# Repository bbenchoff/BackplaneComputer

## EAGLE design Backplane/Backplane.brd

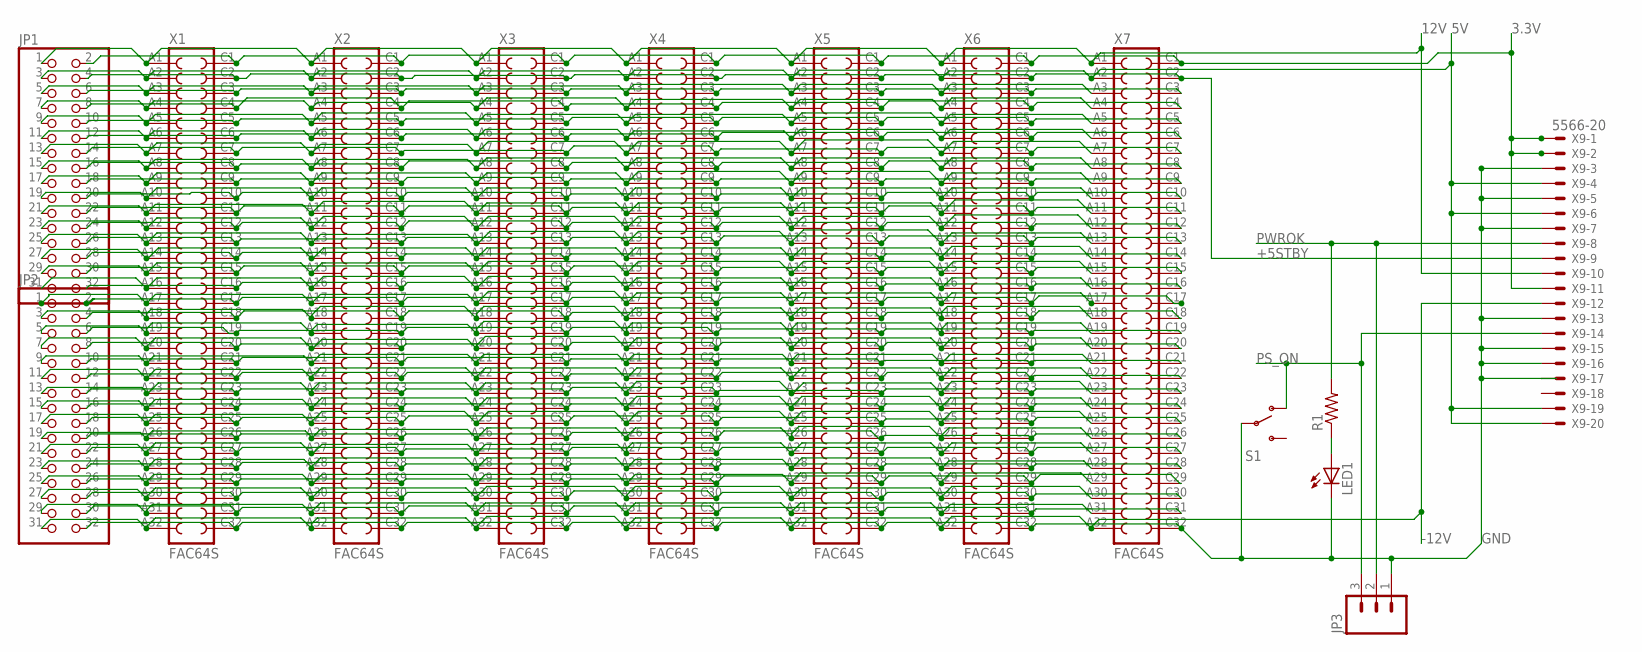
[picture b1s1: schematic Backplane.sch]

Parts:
JP1, JP2: PINHD-2X16; 2X16
JP3: M03LONGPADS; 1X03_LONGPADS
LED1: LED3MM
R1: RESISTORKIT; AXIAL-0.3-KIT
S1: SWITCH-SPDTPTH; SWITCH-SPDT
X1, X2, X3, X4, X5, X6, X7: FAC64S
X9: 5566-20

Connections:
3.3V: JP1.2, X1.C1, X2.C1, X3.C1, X4.C1, X5.C1, X6.C1, X7.C1, X9.1, X9.2, X9.11
5V: JP1.3, X1.A2, X2.A2, X3.A2, X4.A2, X5.A2, X6.A2, X7.A2, X9.4, X9.6, X9.19, X9.20
12V: JP1.1, X1.A1, X2.A1, X3.A1, X4.A1, X5.A1, X6.A1, X7.A1, X9.10
+5STBY: JP1.4, X1.C2, X2.C2, X3.C2, X4.C2, X5.C2, X6.C2, X7.C2, X9.9
-12V: JP2.31, X1.A32, X2.A32, X3.A32, X4.A32, X5.A32, X6.A32, X7.A32, X9.12
GND: JP2.32, JP3.1, LED1.K (C), S1.2, X1.C32, X2.C32, X3.C32, X4.C32, X5.C32, X6.C32, X7.C32, X9.3, X9.5, X9.7, X9.13, X9.15, X9.16
unnamed: LED1.A, R1.P$1 (1)
unnamed: JP1.5, X1.A3, X2.A3, X3.A3, X4.A3, X5.A3, X6.A3, X7.A3
unnamed: JP1.6, X1.C3, X2.C3, X3.C3, X4.C3, X5.C3, X6.C3, X7.C3
unnamed: JP1.7, X1.A4, X2.A4, X3.A4, X4.A4, X5.A4, X6.A4, X7.A4
unnamed: JP1.8, X1.C4, X2.C4, X3.C4, X4.C4, X5.C4, X6.C4, X7.C4
unnamed: JP1.9, X1.A5, X2.A5, X3.A5, X4.A5, X5.A5, X6.A5, X7.A5
unnamed: JP1.10, X1.C5, X2.C5, X3.C5, X4.C5, X5.C5, X6.C5, X7.C5
unnamed: JP1.11, X1.A6, X2.A6, X3.A6, X4.A6, X5.A6, X6.A6, X7.A6
unnamed: JP1.12, X1.C6, X2.C6, X3.C6, X4.C6, X5.C6, X6.C6, X7.C6
unnamed: JP1.13, X1.A7, X2.A7, X3.A7, X4.A7, X5.A7, X6.A7, X7.A7
unnamed: JP1.14, X1.C7, X2.C7, X3.C7, X4.C7, X5.C7, X6.C7, X7.C7
unnamed: JP1.15, X1.A8, X2.A8, X3.A8, X4.A8, X5.A8, X6.A8, X7.A8
unnamed: JP1.16, X1.C8, X2.C8, X3.C8, X4.C8, X5.C8, X6.C8, X7.C8
unnamed: JP1.17, X1.A9, X2.A9, X3.A9, X4.A9, X5.A9, X6.A9, X7.A9
unnamed: JP1.18, X1.C9, X2.C9, X3.C9, X4.C9, X5.C9, X6.C9, X7.C9
unnamed: JP1.19, X1.A10, X2.A10, X3.A10, X4.A10, X5.A10, X6.A10, X7.A10
unnamed: JP1.20, X1.C10, X2.C10, X3.C10, X4.C10, X5.C10, X6.C10, X7.C10
unnamed: JP1.21, X1.A11, X2.A11, X3.A11, X4.A11, X5.A11, X6.A11, X7.A11
unnamed: JP1.22, X1.C11, X2.C11, X3.C11, X4.C11, X5.C11, X6.C11, X7.C11
unnamed: JP1.23, X1.A12, X2.A12, X3.A12, X4.A12, X5.A12, X6.A12, X7.A12
unnamed: JP1.24, X1.C12, X2.C12, X3.C12, X4.C12, X5.C12, X6.C12, X7.C12
unnamed: JP1.25, X1.A13, X2.A13, X3.A13, X4.A13, X5.A13, X6.A13, X7.A13
unnamed: JP1.26, X1.C13, X2.C13, X3.C13, X4.C13, X5.C13, X6.C13, X7.C13
unnamed: JP1.27, X1.A14, X2.A14, X3.A14, X4.A14, X5.A14, X6.A14, X7.A14
unnamed: JP1.28, X1.C14, X2.C14, X3.C14, X4.C14, X5.C14, X6.C14, X7.C14
unnamed: JP1.29, X1.A15, X2.A15, X3.A15, X4.A15, X5.A15, X6.A15, X7.A15
unnamed: JP1.30, X1.C15, X2.C15, X3.C15, X4.C15, X5.C15, X6.C15, X7.C15
unnamed: JP1.31, X1.A16, X2.A16, X3.A16, X4.A16, X5.A16, X6.A16, X7.A16
unnamed: JP1.32, X1.C16, X2.C16, X3.C16, X4.C16, X5.C16, X6.C16, X7.C16
unnamed: JP2.1, X1.A17, X2.A17, X3.A17, X4.A17, X5.A17, X6.A17, X7.A17
unnamed: JP2.2, X1.C17, X2.C17, X3.C17, X4.C17, X5.C17, X6.C17, X7.C17
unnamed: JP2.3, X1.A18, X2.A18, X3.A18, X4.A18, X5.A18, X6.A18, X7.A18
unnamed: JP2.4, X1.C18, X2.C18, X3.C18, X4.C18, X5.C18, X6.C18, X7.C18
unnamed: JP2.5, X1.A19, X2.A19, X3.A19, X4.A19, X5.A19, X6.A19, X7.A19
unnamed: JP2.6, X1.C19, X2.C19, X3.C19, X4.C19, X5.C19, X6.C19, X7.C19
unnamed: JP2.7, X1.A20, X2.A20, X3.A20, X4.A20, X5.A20, X6.A20, X7.A20
unnamed: JP2.8, X1.C20, X2.C20, X3.C20, X4.C20, X5.C20, X6.C20, X7.C20
unnamed: JP2.9, X1.A21, X2.A21, X3.A21, X4.A21, X5.A21, X6.A21, X7.A21
unnamed: JP2.10, X1.C21, X2.C21, X3.C21, X4.C21, X5.C21, X6.C21, X7.C21
unnamed: JP2.11, X1.A22, X2.A22, X3.A22, X4.A22, X5.A22, X6.A22, X7.A22
unnamed: JP2.12, X1.C22, X2.C22, X3.C22, X4.C22, X5.C22, X6.C22, X7.C22
unnamed: JP2.13, X1.A23, X2.A23, X3.A23, X4.A23, X5.A23, X6.A23, X7.A23
unnamed: JP2.14, X1.C23, X2.C23, X3.C23, X4.C23, X5.C23, X6.C23, X7.C23
unnamed: JP2.15, X1.A24, X2.A24, X3.A24, X4.A24, X5.A24, X6.A24, X7.A24
unnamed: JP2.16, X1.C24, X2.C24, X3.C24, X4.C24, X5.C24, X6.C24, X7.C24
unnamed: JP2.17, X1.A25, X2.A25, X3.A25, X4.A25, X5.A25, X6.A25, X7.A25
unnamed: JP2.18, X1.C25, X2.C25, X3.C25, X4.C25, X5.C25, X6.C25, X7.C25
unnamed: JP2.19, X1.A26, X2.A26, X3.A26, X4.A26, X5.A26, X6.A26, X7.A26
unnamed: JP2.20, X1.C26, X2.C26, X3.C26, X4.C26, X5.C26, X6.C26, X7.C26
unnamed: JP2.21, X1.A27, X2.A27, X3.A27, X4.A27, X5.A27, X6.A27, X7.A27
unnamed: JP2.22, X1.C27, X2.C27, X3.C27, X4.C27, X5.C27, X6.C27, X7.C27
unnamed: JP2.23, X1.A28, X2.A28, X3.A28, X4.A28, X5.A28, X6.A28, X7.A28
unnamed: JP2.24, X1.C28, X2.C28, X3.C28, X4.C28, X5.C28, X6.C28, X7.C28
unnamed: JP2.25, X1.A29, X2.A29, X3.A29, X4.A29, X5.A29, X6.A29, X7.A29
unnamed: JP2.26, X1.C29, X2.C29, X3.C29, X4.C29, X5.C29, X6.C29, X7.C29
unnamed: JP2.27, X1.A30, X2.A30, X3.A30, X4.A30, X5.A30, X6.A30, X7.A30
unnamed: JP2.28, X1.C30, X2.C30, X3.C30, X4.C30, X5.C30, X6.C30, X7.C30
unnamed: JP2.29, X1.A31, X2.A31, X3.A31, X4.A31, X5.A31, X6.A31, X7.A31
unnamed: JP2.30, X1.C31, X2.C31, X3.C31, X4.C31, X5.C31, X6.C31, X7.C31
PS_ON: JP3.3, S1.1 (O), X9.14
PWROK: JP3.2, R1.P$2 (2), X9.8

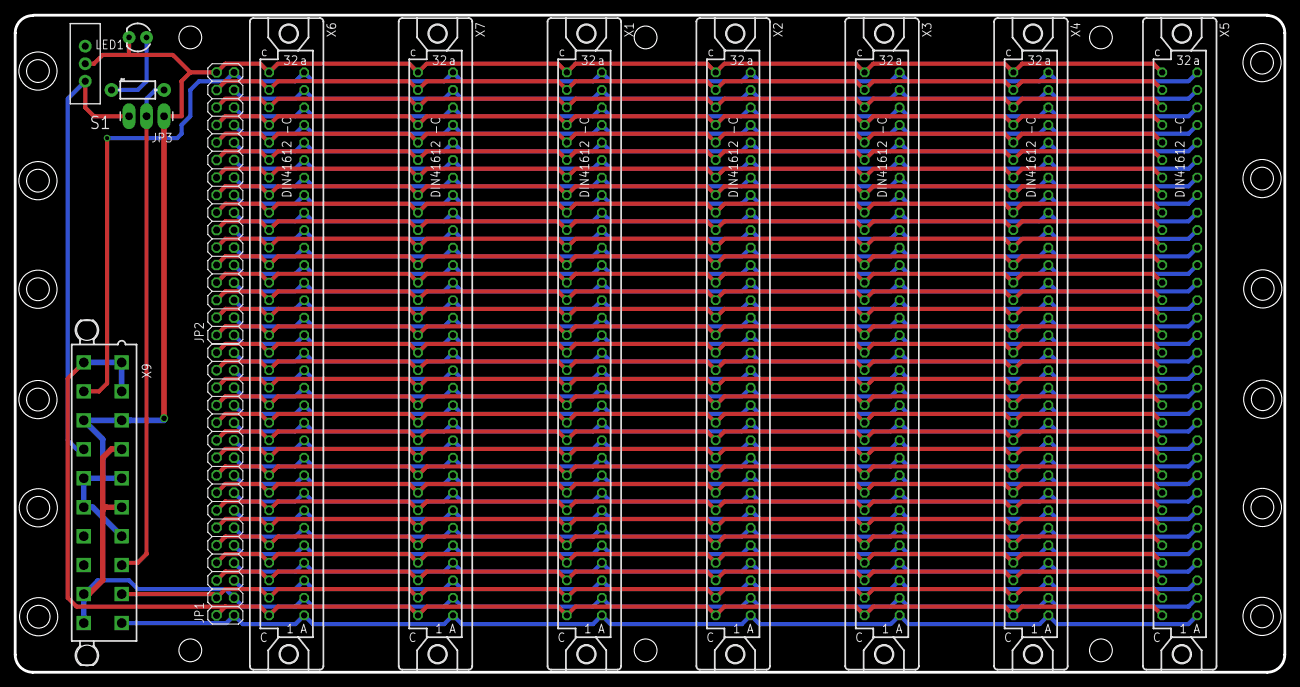
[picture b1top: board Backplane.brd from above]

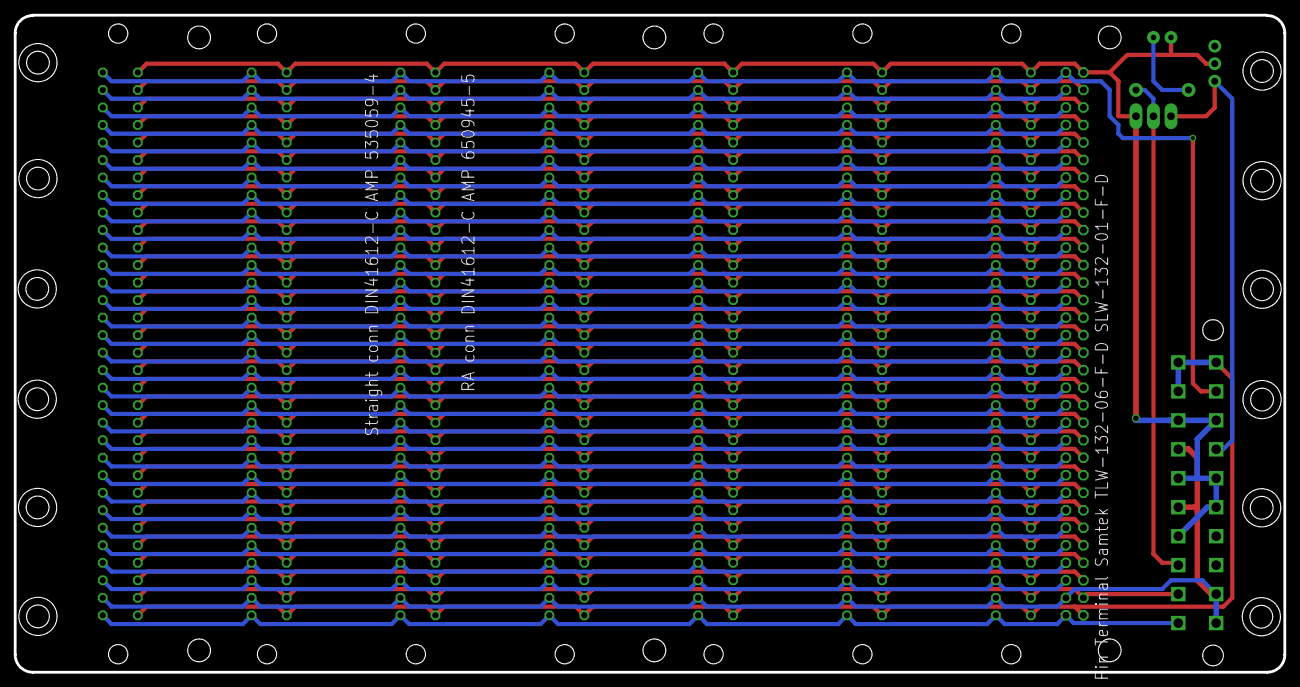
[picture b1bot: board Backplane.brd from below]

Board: 2 copper layers, 184.2 x 95.3 mm, 32 parts (4 on the bottom side), 67 nets.

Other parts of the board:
U$1, U$2, U$3, U$4, U$5, U$6, U$7, U$8, U$9, U$10, U$13, U$14, U$19, U$20, U$21, U$22, U$23, U$24: STAND-OFF

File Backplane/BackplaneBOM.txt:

Part Value   Device         Package       Description              
JP1          .1 SOCKET      2X32          Samtek SLW-132-01-F-D                                                                                 
JP3          M03LONGPADS    1X03_LONGPADS Header 3                                             
LED1         LED3MM         LED3MM        LEDs                                                 
R1           RESISTORKIT    AXIAL-0.3-KIT Resistor                                             
S1           SWITCH-SPDTPTH SWITCH-SPDT   SPDT Switch                                          
X1   FAC64S  FAC64S         FAC64S        CONNECTOR                                            
X2   FAC64S  FAC64S         FAC64S        CONNECTOR                                            
X3   FAC64S  FAC64S         FAC64S        CONNECTOR                                            
X4   FAC64S  FAC64S         FAC64S        CONNECTOR                                            
X5   FAC64S  FAC64S         FAC64S        CONNECTOR                                            
X6   FAC64S  FAC64S         FAC64S        CONNECTOR                                            
X7   FAC64S  FAC64S         FAC64S        CONNECTOR                                            
X9   5566-20 5566-20        5566-20       Mini FIT connector

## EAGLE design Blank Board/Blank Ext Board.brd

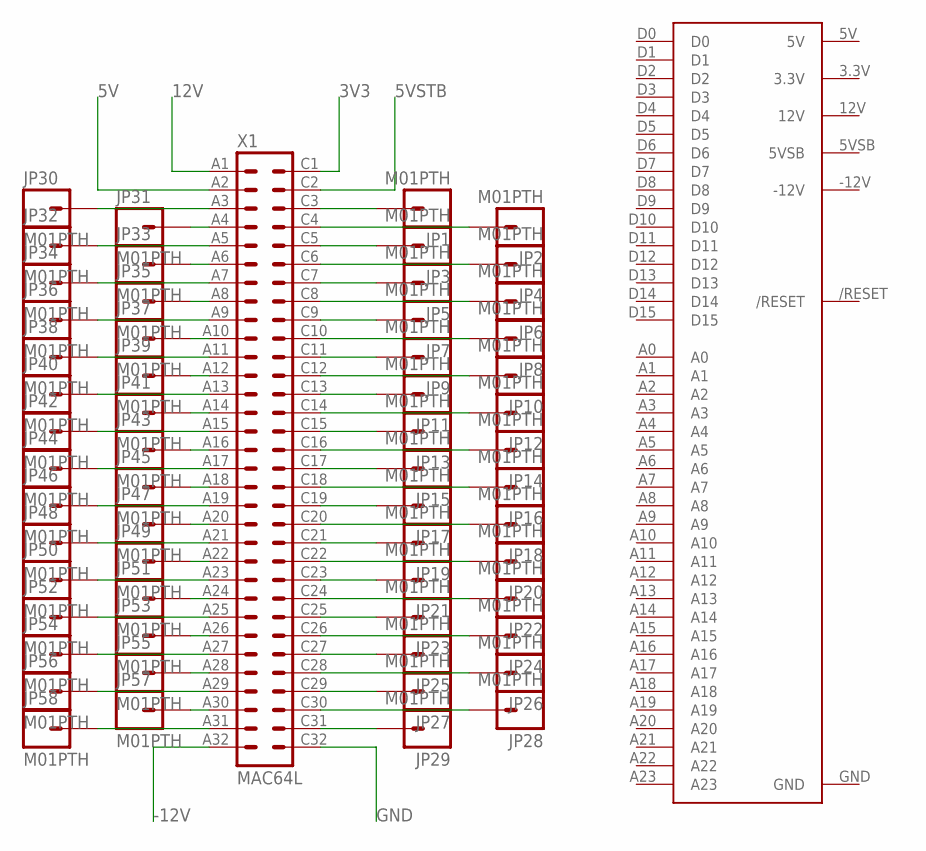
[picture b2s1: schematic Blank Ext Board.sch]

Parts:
JP1, JP2, JP3, JP4, JP5, JP6, JP7, JP8, JP9, JP10, JP11, JP12, JP13, JP14, JP15, JP16, JP17, JP18, JP19, JP20, JP21, JP22, JP23, JP24, JP25, JP26, JP27, JP28, JP29, JP30, JP31, JP32, JP33, JP34, JP35, JP36, JP37, JP38, JP39, JP40, JP41, JP42, JP43, JP44, JP45, JP46, JP47, JP48, JP49, JP50, JP51, JP52, JP53, JP54, JP55, JP56, JP57, JP58: M01PTH; 1X01
U$3: BACKPLANEBOARD
X1: MAC64L

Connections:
3V3: X1.C1
5V: X1.A2
5VSTB: X1.C2
12V: X1.A1
-12V: X1.A32
GND: X1.C32
unnamed: JP58.1, X1.A31
unnamed: JP29.1, X1.C31
unnamed: JP57.1, X1.A30
unnamed: JP28.1, X1.C30
unnamed: JP56.1, X1.A29
unnamed: JP27.1, X1.C29
unnamed: JP55.1, X1.A28
unnamed: JP26.1, X1.C28
unnamed: JP54.1, X1.A27
unnamed: JP25.1, X1.C27
unnamed: JP53.1, X1.A26
unnamed: JP24.1, X1.C26
unnamed: JP52.1, X1.A25
unnamed: JP23.1, X1.C25
unnamed: JP51.1, X1.A24
unnamed: JP22.1, X1.C24
unnamed: JP50.1, X1.A23
unnamed: JP21.1, X1.C23
unnamed: JP49.1, X1.A22
unnamed: JP20.1, X1.C22
unnamed: JP48.1, X1.A21
unnamed: JP19.1, X1.C21
unnamed: JP47.1, X1.A20
unnamed: JP18.1, X1.C20
unnamed: JP46.1, X1.A19
unnamed: JP17.1, X1.C19
unnamed: JP45.1, X1.A18
unnamed: JP16.1, X1.C18
unnamed: JP44.1, X1.A17
unnamed: JP15.1, X1.C17
unnamed: JP14.1, X1.C16
unnamed: JP43.1, X1.A16
unnamed: JP13.1, X1.C15
unnamed: JP42.1, X1.A15
unnamed: JP12.1, X1.C14
unnamed: JP41.1, X1.A14
unnamed: JP11.1, X1.C13
unnamed: JP40.1, X1.A13
unnamed: JP10.1, X1.C12
unnamed: JP39.1, X1.A12
unnamed: JP9.1, X1.C11
unnamed: JP38.1, X1.A11
unnamed: JP8.1, X1.C10
unnamed: JP37.1, X1.A10
unnamed: JP7.1, X1.C9
unnamed: JP36.1, X1.A9
unnamed: JP6.1, X1.C8
unnamed: JP35.1, X1.A8
unnamed: JP5.1, X1.C7
unnamed: JP34.1, X1.A7
unnamed: JP4.1, X1.C6
unnamed: JP33.1, X1.A6
unnamed: JP3.1, X1.C5
unnamed: JP32.1, X1.A5
unnamed: JP2.1, X1.C4
unnamed: JP31.1, X1.A4
unnamed: JP1.1, X1.C3
unnamed: JP30.1, X1.A3

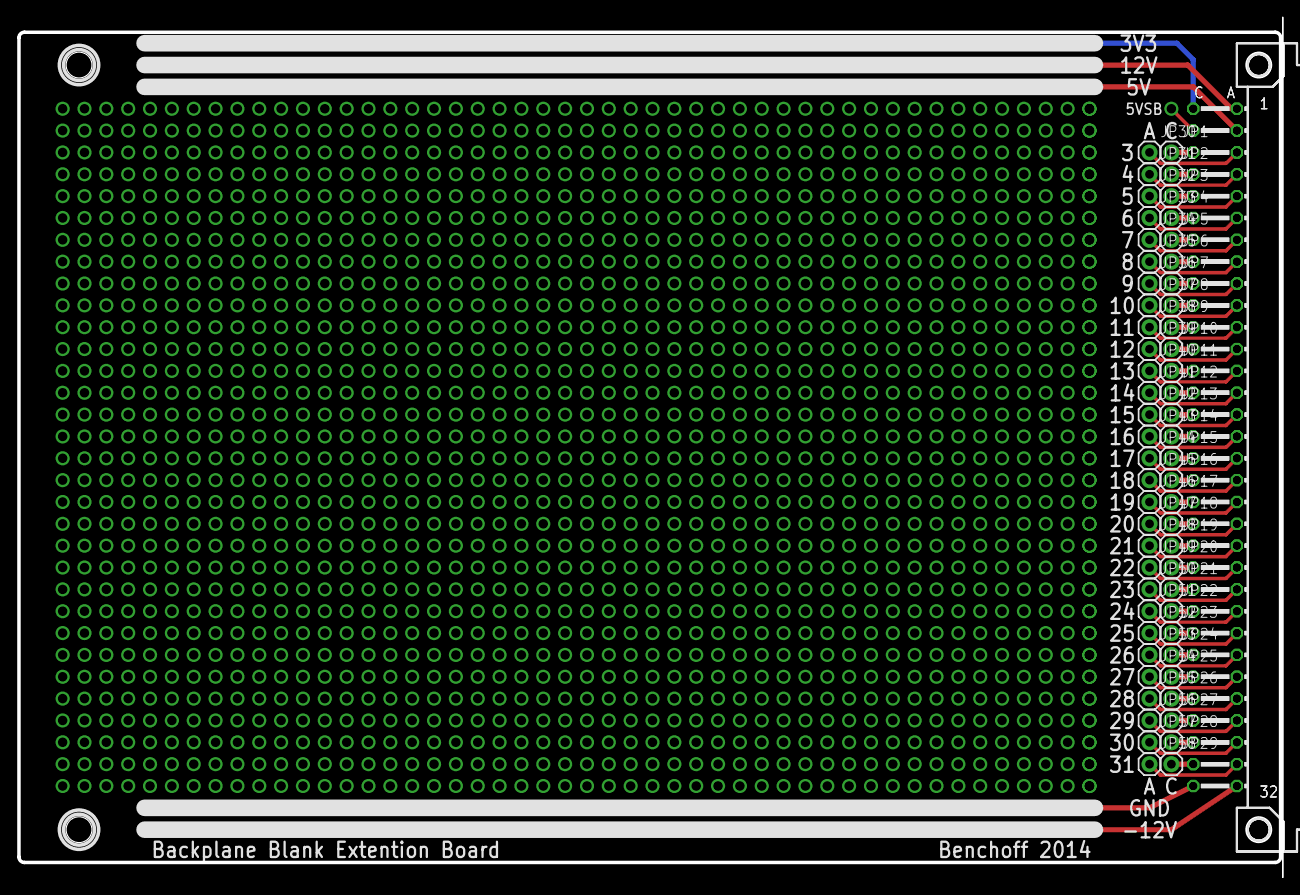
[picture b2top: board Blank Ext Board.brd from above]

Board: 2 copper layers, 146.9 x 100.0 mm, 60 parts (0 on the bottom side), 58 nets.

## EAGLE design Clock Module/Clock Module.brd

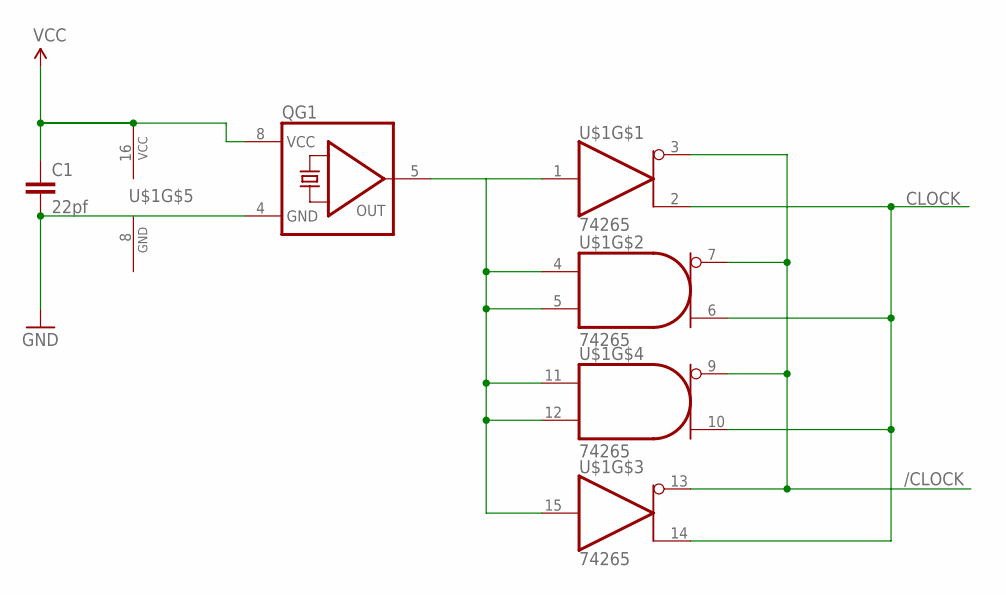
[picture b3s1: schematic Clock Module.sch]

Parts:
C1: 22pf; CAP-PTH-SMALLEZ
QG1: QG5460; DIL08S
U$1: 74265; DIL16

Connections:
/CLOCK: U$1.3 (Y), U$1.7 (Y), U$1.9 (Y), U$1.13 (Y)
CLOCK: U$1.2 (W), U$1.6 (W), U$1.10 (W), U$1.14 (W)
GND: C1.2, QG1.4 (GND), U$1.8 (GND)
unnamed: QG1.5 (OUT), U$1.1 (I), U$1.4 (A), U$1.5 (B), U$1.11 (A), U$1.12 (B), U$1.15 (I)
VCC: C1.1, QG1.8 (VCC), U$1.16 (VCC)

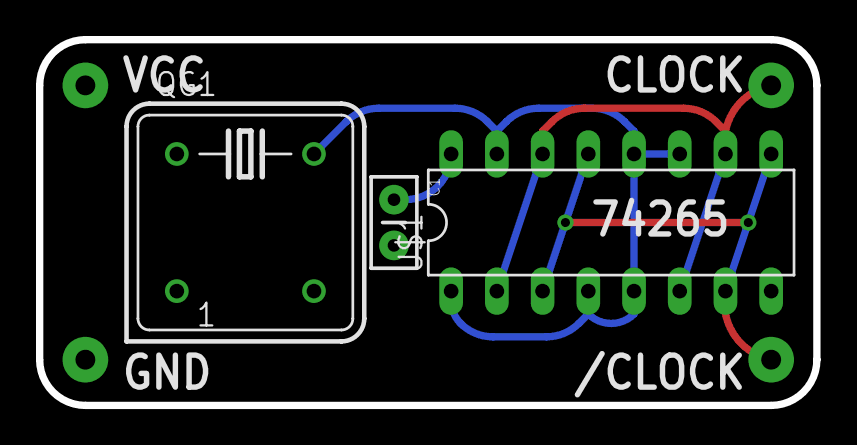
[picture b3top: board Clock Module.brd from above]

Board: 2 copper layers, 43.2 x 20.3 mm, 3 parts (0 on the bottom side), 5 nets.

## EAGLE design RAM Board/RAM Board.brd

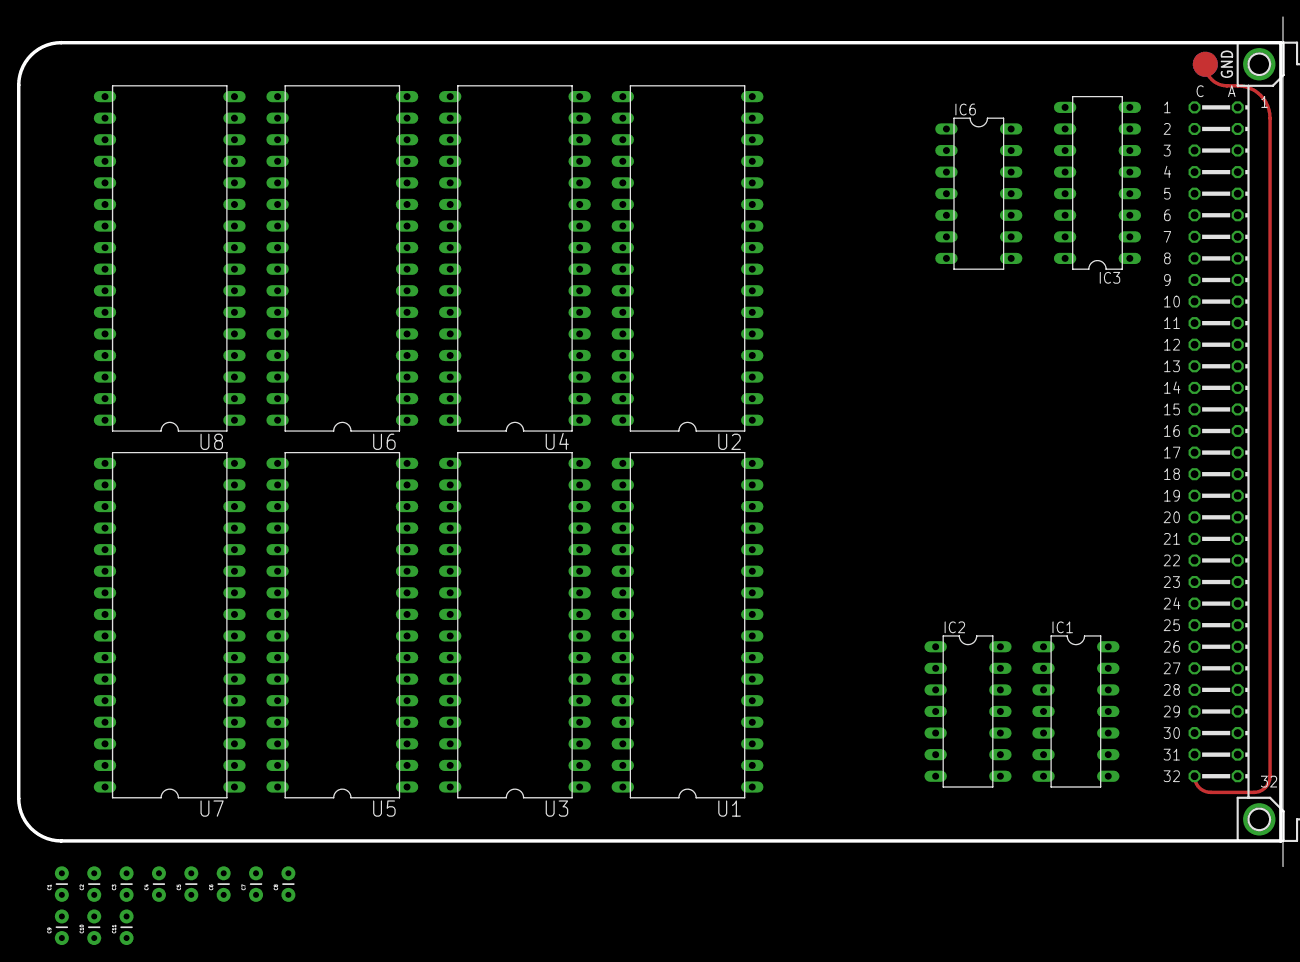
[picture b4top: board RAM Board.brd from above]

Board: 2 copper layers, 148.8 x 100.0 mm, 24 parts (0 on the bottom side), 57 nets, no tracks yet.

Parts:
C1, C2, C3, C4, C5, C6, C7, C8, C9, C10, C11: 100nF; CAP-PTH-SMALL
IC1, IC6: 74LS32N; DIL14
IC2: 74LS04N; DIL14
IC3: 74LS138N; DIL16
U1, U2, U3, U4, U5, U6, U7, U8: AS6C4008; DIL32
U$1: BLANKBOARD

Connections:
/AS: IC3.1, U$1./AS
/BOOT: IC6.1, IC6.4, IC6.9, IC6.12
/LDS: IC1.4, IC1.12, U$1./LDS
/UDS: IC1.1, IC1.9, U$1./UDS
ADDRESS0: U1.12, U2.12, U3.12, U4.12, U5.12, U6.12, U7.12, U8.12, U$1.A0
ADDRESS1: U1.11, U2.11, U3.11, U4.11, U5.11, U6.11, U7.11, U8.11, U$1.A1
ADDRESS2: U1.10, U2.10, U3.10, U4.10, U5.10, U6.10, U7.10, U8.10, U$1.A2
ADDRESS3: U1.9, U2.9, U3.9, U4.9, U5.9, U6.9, U7.9, U8.9, U$1.A3
ADDRESS4: U1.8, U2.8, U3.8, U4.8, U5.8, U6.8, U7.8, U8.8, U$1.A4
ADDRESS5: U1.7, U2.7, U3.7, U4.7, U5.7, U6.7, U7.7, U8.7, U$1.A5
ADDRESS6: U1.6, U2.6, U3.6, U4.6, U5.6, U6.6, U7.6, U8.6, U$1.A6
ADDRESS7: U1.5, U2.5, U3.5, U4.5, U5.5, U6.5, U7.5, U8.5, U$1.A7
ADDRESS8: U1.27, U2.27, U3.27, U4.27, U5.27, U6.27, U7.27, U8.27, U$1.A8
ADDRESS9: U1.26, U2.26, U3.26, U4.26, U5.26, U6.26, U7.26, U8.26, U$1.A9
ADDRESS10: U1.23, U2.23, U3.23, U4.23, U5.23, U6.23, U7.23, U8.23, U$1.A10
ADDRESS11: U1.25, U2.25, U3.25, U4.25, U5.25, U6.25, U7.25, U8.25, U$1.A11
ADDRESS12: U1.4, U2.4, U3.4, U4.4, U5.4, U6.4, U7.4, U8.4, U$1.A12
ADDRESS13: U1.28, U2.28, U3.28, U4.28, U5.28, U6.28, U7.28, U8.28, U$1.A13
ADDRESS14: U1.3, U2.3, U3.3, U4.3, U5.3, U6.3, U7.3, U8.3, U$1.A14
ADDRESS15: U1.31, U2.31, U3.31, U4.31, U5.31, U6.31, U7.31, U8.31, U$1.A15
ADDRESS16: U1.2, U2.2, U3.2, U4.2, U5.2, U6.2, U7.2, U8.2, U$1.A16
ADDRESS17: U1.30, U2.30, U3.30, U4.30, U5.30, U6.30, U7.30, U8.30, U$1.A17
ADDRESS18: U1.1, U2.1, U3.1, U4.1, U5.1, U6.1, U7.1, U8.1, U$1.A18
ADDRESS20: IC3.2, U$1.A20
ADDRESS21: IC3.3, U$1.A21
BANKACS: IC6.6, U1.22, U2.22
BANKBCS: IC6.11, U3.22, U4.22
BANKCCS: IC6.8, U5.22, U6.22
BANKDCS: IC6.3, U7.22, U8.22
DATA0: U2.13, U4.13, U6.13, U8.13, U$1.D0
DATA1: U2.14, U4.14, U6.14, U8.14, U$1.D1
DATA2: U2.15, U4.15, U6.15, U8.15, U$1.D2
DATA3: U2.17, U4.17, U6.17, U8.17, U$1.D3
DATA4: U2.18, U4.18, U6.18, U8.18, U$1.D4
DATA5: U2.19, U4.19, U6.19, U8.19, U$1.D5
DATA6: U2.20, U4.20, U6.20, U8.20, U$1.D6
DATA7: U2.21, U4.21, U6.21, U8.21, U$1.D7
DATA8: U1.13, U3.13, U5.13, U7.13, U$1.D8
DATA9: U1.14, U3.14, U5.14, U7.14, U$1.D9
DATA10: U1.15, U3.15, U5.15, U7.15, U$1.D10
DATA11: U1.17, U3.17, U5.17, U7.17, U$1.D11
DATA12: U1.18, U3.18, U5.18, U7.18, U$1.D12
DATA13: U1.19, U3.19, U5.19, U7.19, U$1.D13
DATA14: U1.20, U3.20, U5.20, U7.20, U$1.D14
DATA15: U1.21, U3.21, U5.21, U7.21, U$1.D15
GND: C1.2, C2.2, C3.2, C4.2, C5.2, C6.2, C7.2, C8.2, C9.2, C10.2, C11.2, IC1.7, IC2.7, IC3.4, IC3.5, IC3.8, IC6.7, U1.16, U2.16, U3.16, U4.16, U5.16, U6.16, U7.16, U8.16, U$1.GND
unnamed: IC1.2, IC1.5, IC2.2
unnamed: IC3.9, IC6.2
unnamed: IC3.11, IC6.10
unnamed: IC3.13, IC6.13
unnamed: IC3.15, IC6.5
R/W: IC1.10, IC1.13, IC2.1, U$1.R/W
READHI: IC1.3, U1.24, U3.24, U5.24, U7.24
READLO: IC1.6, U2.24, U4.24, U6.24, U8.24
VCC: C1.1, C2.1, C3.1, C4.1, C5.1, C6.1, C7.1, C8.1, C9.1, C10.1, C11.1, IC1.14, IC2.14, IC3.6, IC3.16, IC6.14, U1.32, U2.32, U3.32, U4.32, U5.32, U6.32, U7.32, U8.32, U$1.5V
WRITEHI: IC1.8, U1.29, U3.29, U5.29, U7.29
WRITELO: IC1.11, U2.29, U4.29, U6.29, U8.29

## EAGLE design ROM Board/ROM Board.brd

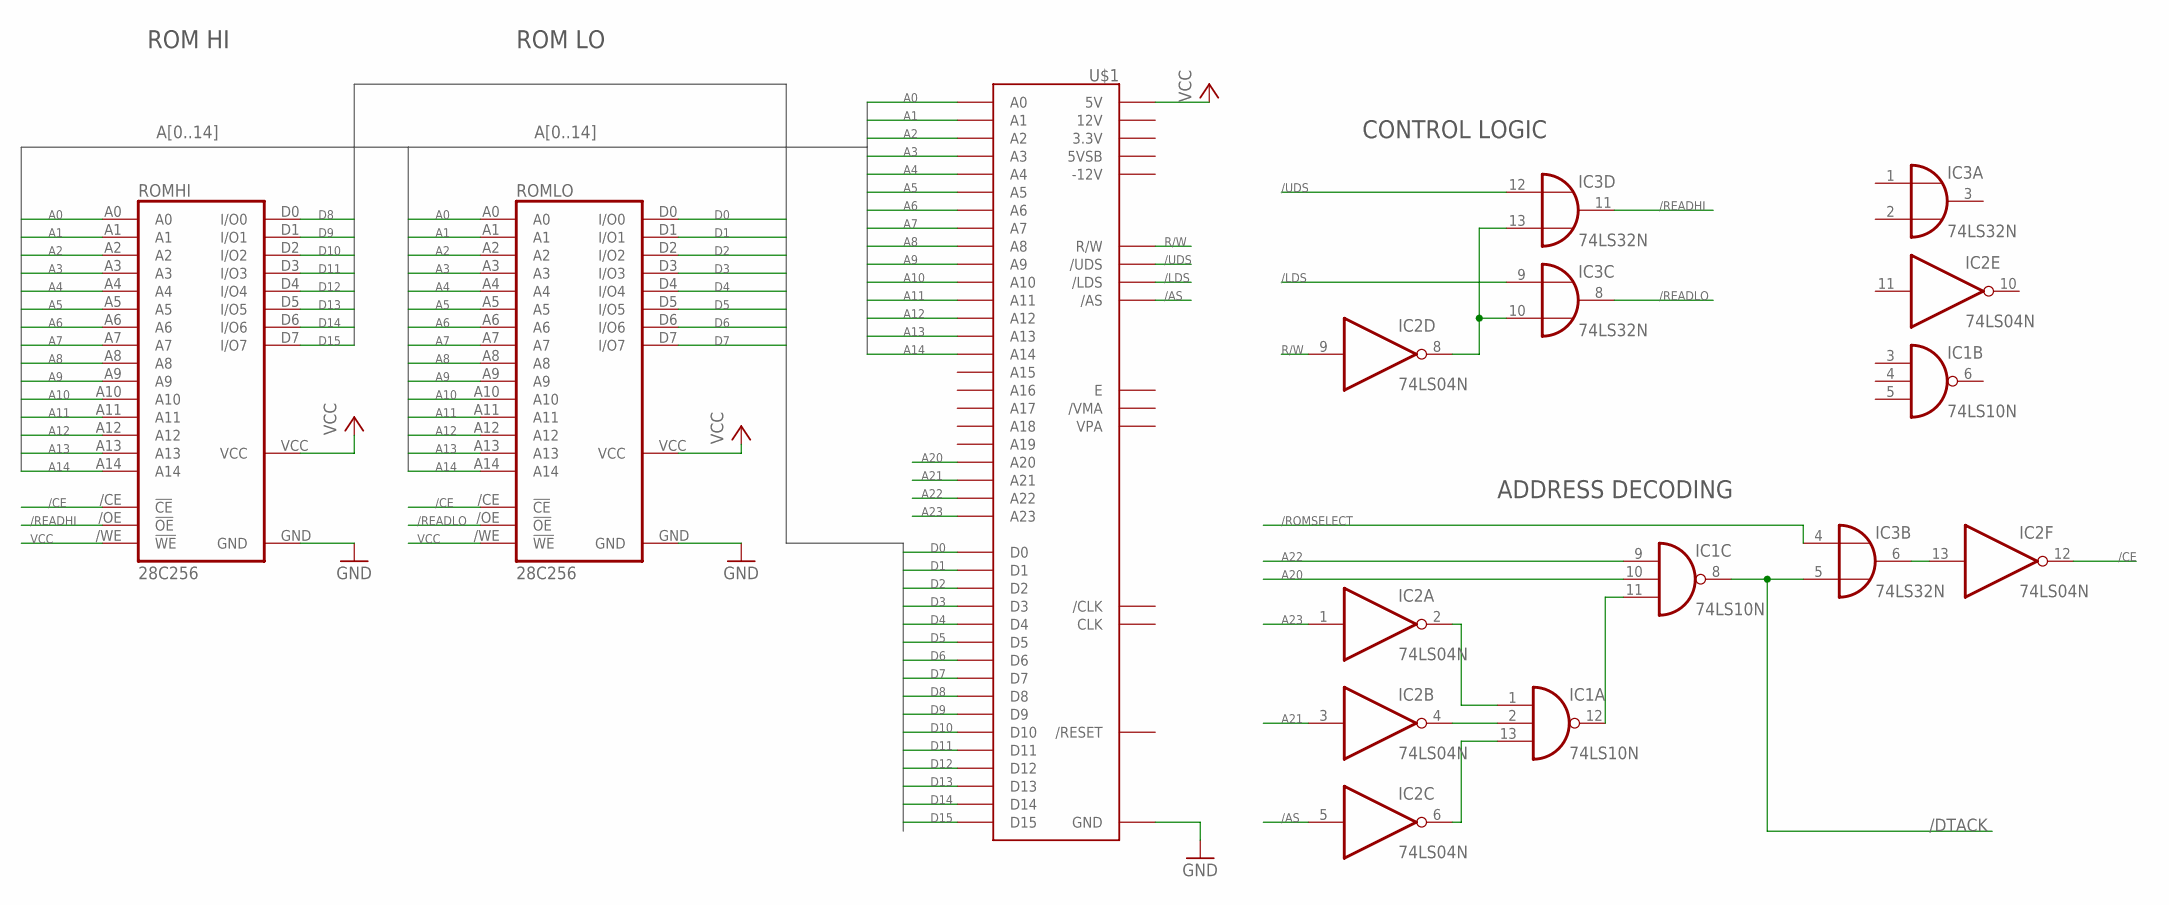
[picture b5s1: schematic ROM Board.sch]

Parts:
IC1: 74LS10N; DIL14
IC2: 74LS04N; DIL14
IC3: 74LS32N; DIL14
ROMHI: 28C256; DIL28-6
ROMLO: 28C256; DIL28-6
U$1: BLANKBOARD

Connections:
/AS: IC2.5 (I), U$1./AS
/CE: IC2.12 (O), ROMHI./CE (!CE), ROMLO./CE (!CE)
/LDS: IC3.9 (I0), U$1./LDS
/READHI: IC3.11 (O), ROMHI./OE (!OE)
/READLO: IC3.8 (O), ROMLO./OE (!OE)
/ROMSELECT: IC3.4 (I0)
/UDS: IC3.12 (I0), U$1./UDS
A0: ROMHI.A0, ROMLO.A0, U$1.A0
A1: ROMHI.A1, ROMLO.A1, U$1.A1
A2: ROMHI.A2, ROMLO.A2, U$1.A2
A3: ROMHI.A3, ROMLO.A3, U$1.A3
A4: ROMHI.A4, ROMLO.A4, U$1.A4
A5: ROMHI.A5, ROMLO.A5, U$1.A5
A6: ROMHI.A6, ROMLO.A6, U$1.A6
A7: ROMHI.A7, ROMLO.A7, U$1.A7
A8: ROMHI.A8, ROMLO.A8, U$1.A8
A9: ROMHI.A9, ROMLO.A9, U$1.A9
A10: ROMHI.A10, ROMLO.A10, U$1.A10
A11: ROMHI.A11, ROMLO.A11, U$1.A11
A12: ROMHI.A12, ROMLO.A12, U$1.A12
A13: ROMHI.A13, ROMLO.A13, U$1.A13
A14: ROMHI.A14, ROMLO.A14, U$1.A14
A20: IC1.10 (I1), U$1.A20
A21: IC2.3 (I), U$1.A21
A22: IC1.9 (I0), U$1.A22
A23: IC2.1 (I), U$1.A23
D0: ROMLO.D0 (I/O0), U$1.D0
D1: ROMLO.D1 (I/O1), U$1.D1
D2: ROMLO.D2 (I/O2), U$1.D2
D3: ROMLO.D3 (I/O3), U$1.D3
D4: ROMLO.D4 (I/O4), U$1.D4
D5: ROMLO.D5 (I/O5), U$1.D5
D6: ROMLO.D6 (I/O6), U$1.D6
D7: ROMLO.D7 (I/O7), U$1.D7
D8: ROMHI.D0 (I/O0), U$1.D8
D9: ROMHI.D1 (I/O1), U$1.D9
D10: ROMHI.D2 (I/O2), U$1.D10
D11: ROMHI.D3 (I/O3), U$1.D11
D12: ROMHI.D4 (I/O4), U$1.D12
D13: ROMHI.D5 (I/O5), U$1.D13
D14: ROMHI.D6 (I/O6), U$1.D14
D15: ROMHI.D7 (I/O7), U$1.D15
DECODEOUT: IC1.8 (O), IC3.5 (I1)
GND: IC1.7 (GND), IC2.7 (GND), IC3.7 (GND), ROMHI.GND, ROMLO.GND, U$1.GND
unnamed: IC1.1 (I0), IC2.2 (O)
unnamed: IC1.2 (I1), IC2.4 (O)
unnamed: IC1.13 (I2), IC2.6 (O)
unnamed: IC1.11 (I2), IC1.12 (O)
unnamed: IC2.13 (I), IC3.6 (O)
unnamed: IC2.8 (O), IC3.10 (I1), IC3.13 (I1)
R/W: IC2.9 (I), U$1.R/W
VCC: IC1.14 (VCC), IC2.14 (VCC), IC3.14 (VCC), ROMHI./WE (!WE), ROMHI.VCC, ROMLO./WE (!WE), ROMLO.VCC, U$1.5V

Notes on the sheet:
ROM HI
ROM LO
ADDRESS DECODING
CONTROL LOGIC
/DTACK

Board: 2 copper layers, 6 parts (0 on the bottom side), 51 nets, no tracks yet.

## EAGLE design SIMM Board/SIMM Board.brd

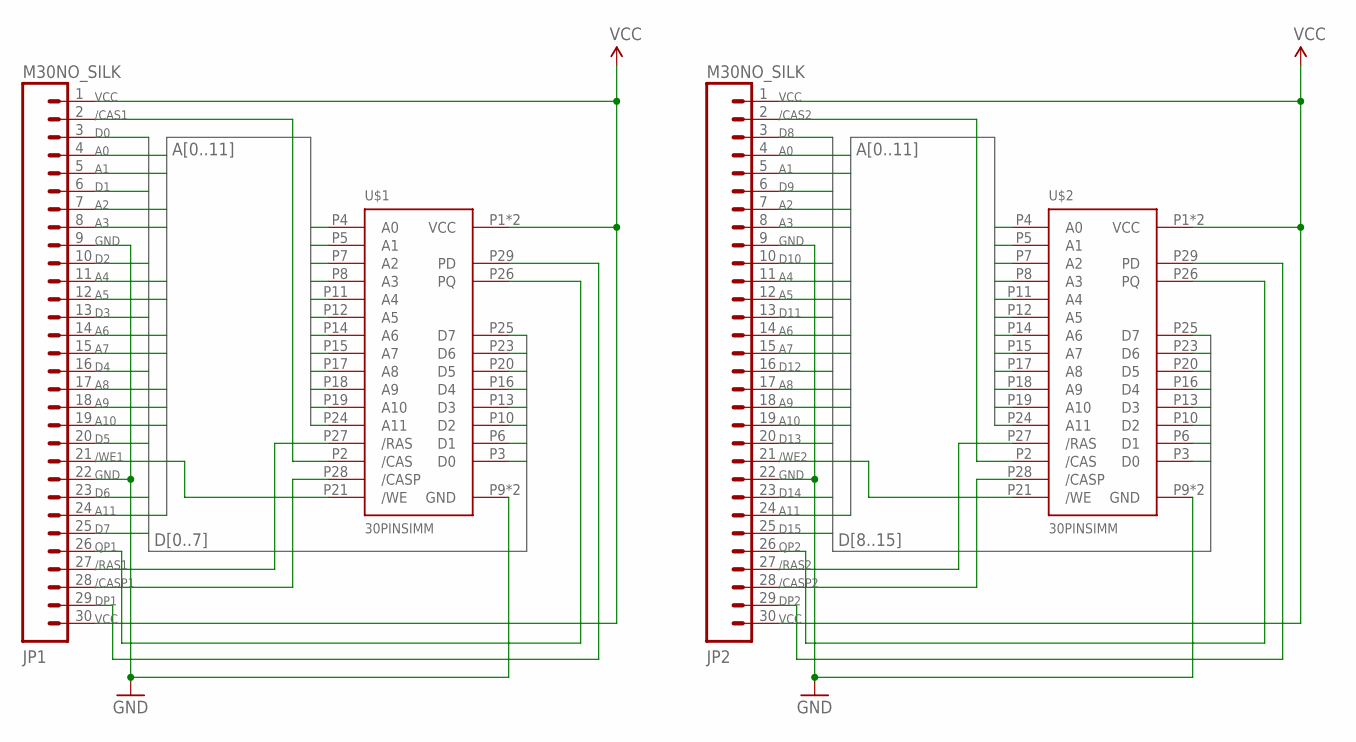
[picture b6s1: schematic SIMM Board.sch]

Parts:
JP1, JP2: M30NO_SILK; 1X30_NO_SILK
U$1, U$2: 30PINSIMM

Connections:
/CAS1: JP1.2, U$1.P2 (/CAS)
/CAS2: JP2.2, U$2.P2 (/CAS)
/CASP1: JP1.28, U$1.P28 (/CASP)
/CASP2: JP2.28, U$2.P28 (/CASP)
/RAS1: JP1.27, U$1.P27 (/RAS)
/RAS2: JP2.27, U$2.P27 (/RAS)
/WE1: JP1.21, U$1.P21 (/WE)
/WE2: JP2.21, U$2.P21 (/WE)
A0: JP1.4, JP2.4, U$1.P4 (A0), U$2.P4 (A0)
A1: JP1.5, JP2.5, U$1.P5 (A1), U$2.P5 (A1)
A2: JP1.7, JP2.7, U$1.P7 (A2), U$2.P7 (A2)
A3: JP1.8, JP2.8, U$1.P8 (A3), U$2.P8 (A3)
A4: JP1.11, JP2.11, U$1.P11 (A4), U$2.P11 (A4)
A5: JP1.12, JP2.12, U$1.P12 (A5), U$2.P12 (A5)
A6: JP1.14, JP2.14, U$1.P14 (A6), U$2.P14 (A6)
A7: JP1.15, JP2.15, U$1.P15 (A7), U$2.P15 (A7)
A8: JP1.17, JP2.17, U$1.P17 (A8), U$2.P17 (A8)
A9: JP1.18, JP2.18, U$1.P18 (A9), U$2.P18 (A9)
A10: JP1.19, JP2.19, U$1.P19 (A10), U$2.P19 (A10)
A11: JP1.24, JP2.24, U$1.P24 (A11), U$2.P24 (A11)
D0: JP1.3, U$1.P3 (D0)
D1: JP1.6, U$1.P6 (D1)
D2: JP1.10, U$1.P10 (D2)
D3: JP1.13, U$1.P13 (D3)
D4: JP1.16, U$1.P16 (D4)
D5: JP1.20, U$1.P20 (D5)
D6: JP1.23, U$1.P23 (D6)
D7: JP1.25, U$1.P25 (D7)
D8: JP2.3, U$2.P3 (D0)
D9: JP2.6, U$2.P6 (D1)
D10: JP2.10, U$2.P10 (D2)
D11: JP2.13, U$2.P13 (D3)
D12: JP2.16, U$2.P16 (D4)
D13: JP2.20, U$2.P20 (D5)
D14: JP2.23, U$2.P23 (D6)
D15: JP2.25, U$2.P25 (D7)
DP1: JP1.29, U$1.P29 (PD)
DP2: JP2.29, U$2.P29 (PD)
GND: JP1.9, JP1.22, JP2.9, JP2.22, U$1.P9 (GND), U$1.P22 (GND), U$2.P9 (GND), U$2.P22 (GND)
QP1: JP1.26, U$1.P26 (PQ)
QP2: JP2.26, U$2.P26 (PQ)
VCC: JP1.1, JP1.30, JP2.1, JP2.30, U$1.P1 (VCC), U$1.P30 (VCC), U$2.P1 (VCC), U$2.P30 (VCC)

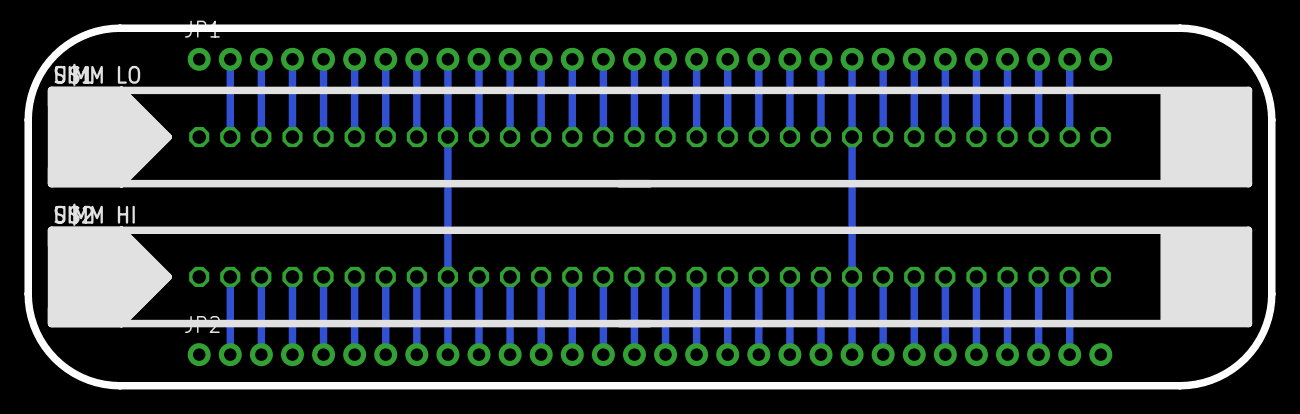
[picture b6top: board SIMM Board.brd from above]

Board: 2 copper layers, 101.6 x 29.2 mm, 4 parts (0 on the bottom side), 42 nets.

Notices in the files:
parts and their libraries:
SparkFun-Electromechanical: Licensing: CC v3.0 Share-Alike You are welcome to use this library for commercial purposes.
